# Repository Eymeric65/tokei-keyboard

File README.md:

# tokei-keyboard
Official repository of the Tokei split keyboard.

This repository is split in the different component in order to make a working Tokei Split keyboard.

*If you are searching the kicad library used in this keyboard you should go to [this repository]*

## Kicad / PCB 

If you directly want to order your board you should directly check [JLCPCB production archive](/kicad/OUTPUT/final-JLCPCB.zip)

Otherwise Kicad project is divided in three :
- The left half
- The right half
- The paneliser to reunion both for production

Electrical output is stored into the **`JLCPCB`** directory, CAD related output is stored in **`CAD`** folder (don't hesitate to check)

## firmware

The `firmware` folder contain ready to flash files in order to test right away the keyboard.

## ZMK

The `zmk-config` file is a direct copy of my `zmk-config` fork for this keyboard. It is the base to the build of the keyboard.

## CAD 

The `CAD` folder contain everything related with the 3D printed cover. I work with Alibre but you can find the ready-to-use `.step` in the `CAD/export` folder.

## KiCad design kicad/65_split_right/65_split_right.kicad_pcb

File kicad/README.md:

Here you can find both of the Kicad project for the right and left halves of the keyboard.
There is also the result of the paneliser in order to merge both halves (cheaper).

I would advise to check the board with your supplier.

If you trust me entirely you can directly use the archive [JLCPC accepted gerber](/OUTPUT/final-JLCPCB.zip) (for reference $32.37 for 5 boards)

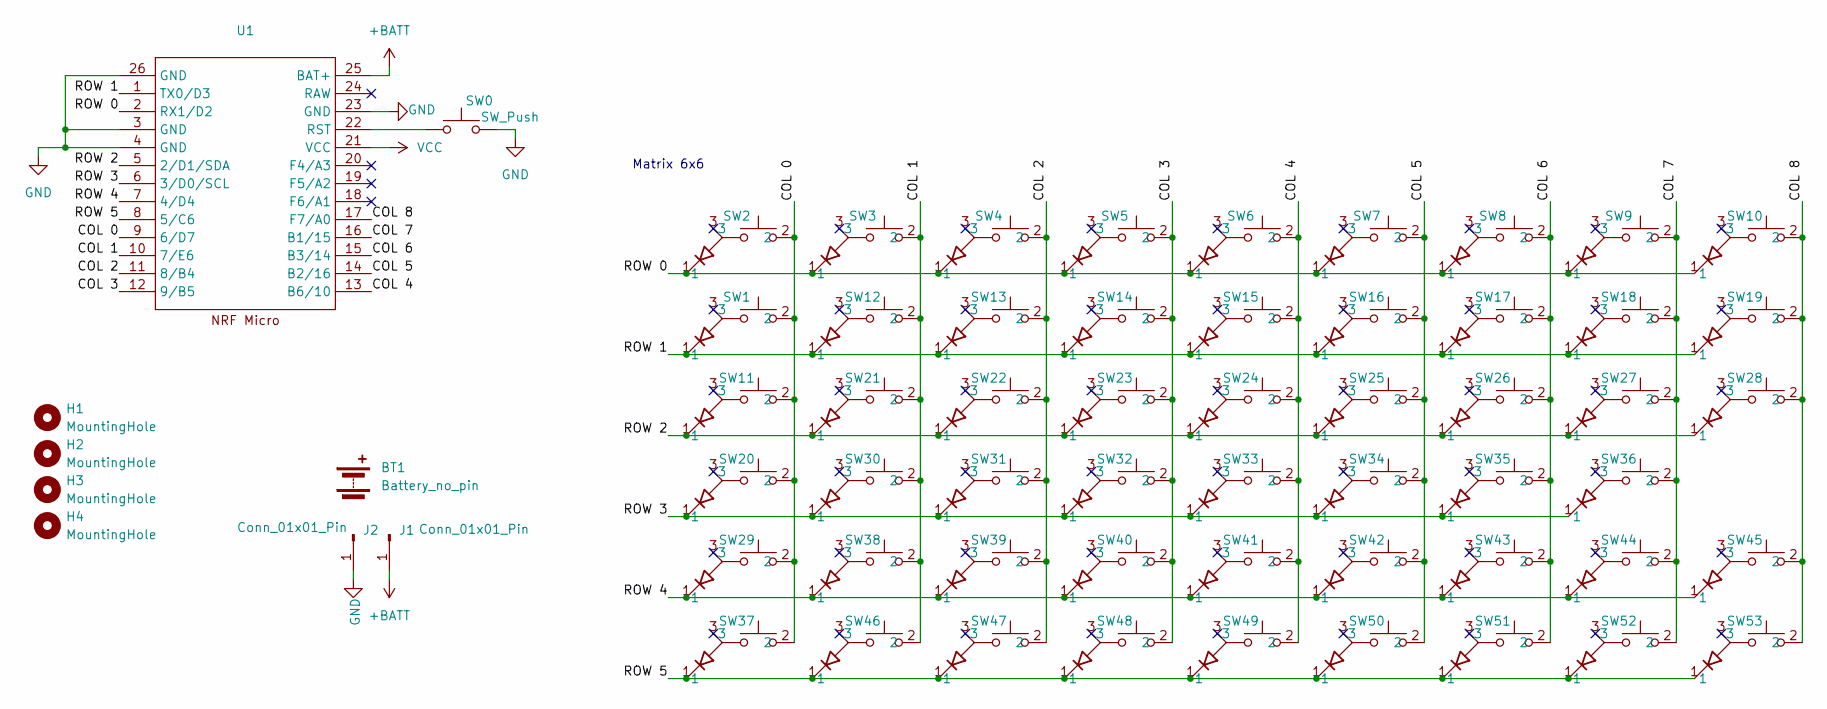
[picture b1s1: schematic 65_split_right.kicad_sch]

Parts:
BT1: Battery_no_pin; 503020 battery hole
H1, H2, H3, H4: MountingHole; MountingHole_2.2mm_M2_DIN965
J1, J2: Conn_01x01_Pin; Pin_D1.0mm_L10.0mm
SW0: SW_Push; Reset_Switch
SW1, SW2, SW3, SW4, SW5, SW6, SW7, SW8, SW9, SW10, SW11, SW12, SW13, SW14, SW15, SW16, SW17, SW19, SW20, SW21, SW22, SW23, SW24, SW25, SW26, SW28, SW29, SW30, SW31, SW32, SW33, SW34, SW36, SW37, SW38, SW39, SW40, SW41, SW42, SW44, SW45, SW47, SW48, SW49, SW50, SW51, SW52, SW53: SW_UNIVERSAL_1.00u_PCB
SW18, SW46: SW_UNIVERSAL_2.00u_PCB
SW27: SW_UNIVERSAL_1.50u_PCB
SW35: SW_UNIVERSAL_2.25u_PCB
SW43: SW_UNIVERSAL_1.75u_PCB
U1: ProMicro_DUAL

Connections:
+BATT: J1.1, U1.25 (BAT+)
/COL 0: SW1.2, SW2.2, SW11.2, SW20.2, SW29.2, SW37.2, U1.9 (6/D7)
/COL 1: SW3.2, SW12.2, SW21.2, SW30.2, SW38.2, SW46.2, U1.10 (7/E6)
/COL 2: SW4.2, SW13.2, SW22.2, SW31.2, SW39.2, SW47.2, U1.11 (8/B4)
/COL 3: SW5.2, SW14.2, SW23.2, SW32.2, SW40.2, SW48.2, U1.12 (9/B5)
/COL 4: SW6.2, SW15.2, SW24.2, SW33.2, SW41.2, SW49.2, U1.13 (B6/10)
/COL 5: SW7.2, SW16.2, SW25.2, SW34.2, SW42.2, SW50.2, U1.14 (B2/16)
/COL 6: SW8.2, SW17.2, SW26.2, SW35.2, SW43.2, SW51.2, U1.15 (B3/14)
/COL 7: SW9.2, SW18.2, SW27.2, SW36.2, SW44.2, SW52.2, U1.16 (B1/15)
/COL 8: SW10.2, SW19.2, SW28.2, SW45.2, SW53.2, U1.17 (F7/A0)
/ROW 0: SW2.1, SW3.1, SW4.1, SW5.1, SW6.1, SW7.1, SW8.1, SW9.1, SW10.1, U1.2 (RX1/D2)
/ROW 1: SW1.1, SW12.1, SW13.1, SW14.1, SW15.1, SW16.1, SW17.1, SW18.1, SW19.1, U1.1 (TX0/D3)
/ROW 2: SW11.1, SW21.1, SW22.1, SW23.1, SW24.1, SW25.1, SW26.1, SW27.1, SW28.1, U1.5 (2/D1/SDA)
/ROW 3: SW20.1, SW30.1, SW31.1, SW32.1, SW33.1, SW34.1, SW35.1, SW36.1, U1.6 (3/D0/SCL)
/ROW 4: SW29.1, SW38.1, SW39.1, SW40.1, SW41.1, SW42.1, SW43.1, SW44.1, SW45.1, U1.7 (4/D4)
/ROW 5: SW37.1, SW46.1, SW47.1, SW48.1, SW49.1, SW50.1, SW51.1, SW52.1, SW53.1, U1.8 (5/C6)
GND: J2.1, SW0.2, U1.3 (GND), U1.4 (GND), U1.23 (GND), U1.26 (GND)
unnamed: SW0.1, U1.22 (RST)
VCC: U1.21 (VCC)

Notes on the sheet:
Matrix 6x6

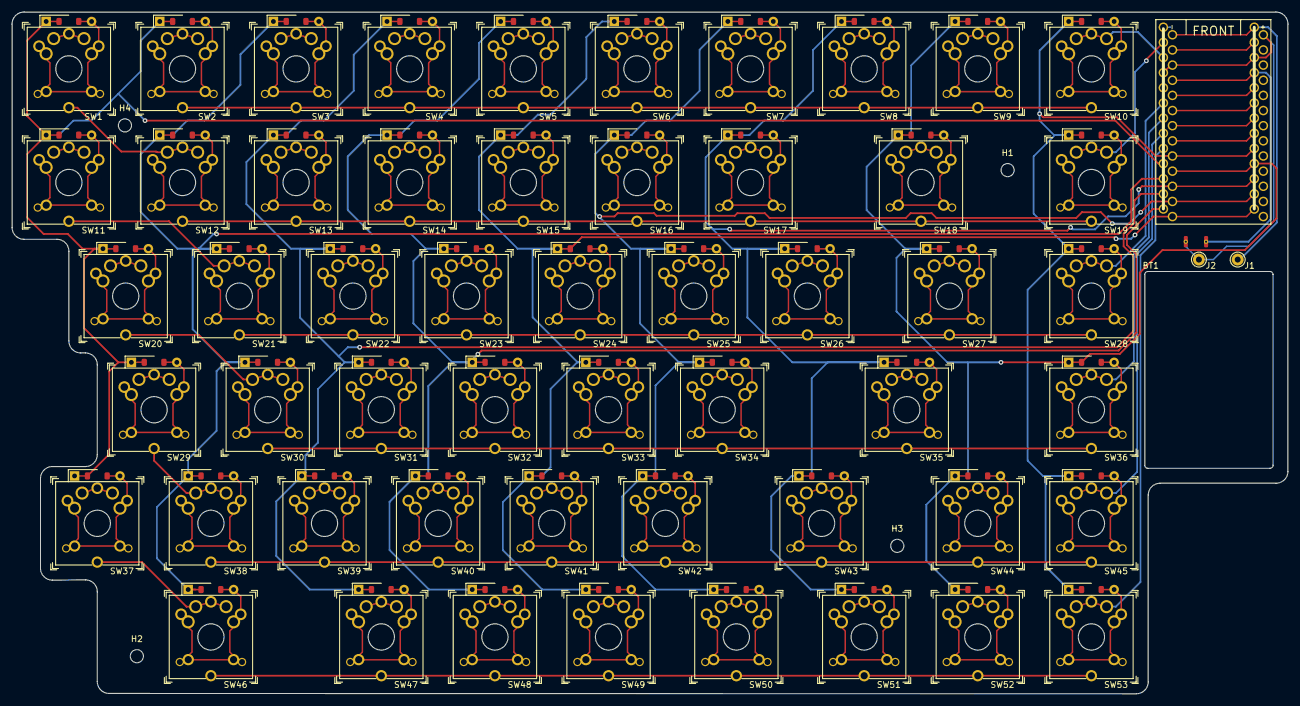
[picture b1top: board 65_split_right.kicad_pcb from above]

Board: 2 copper layers, 213.9 x 114.2 mm, 62 parts (1 on the bottom side), 18 nets.

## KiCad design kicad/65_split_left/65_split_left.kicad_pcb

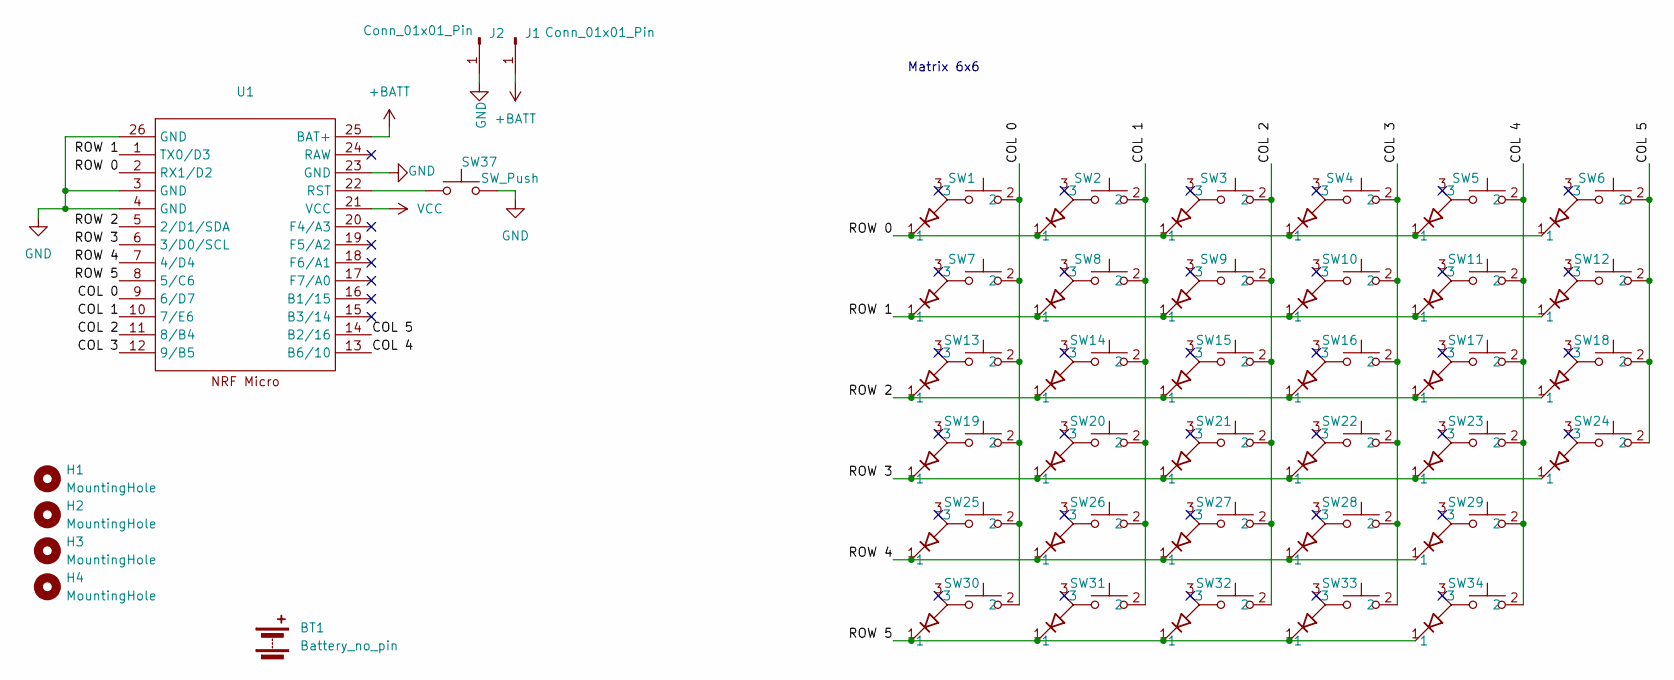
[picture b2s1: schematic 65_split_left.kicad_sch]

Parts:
BT1: Battery_no_pin; 503020 battery hole
H1, H2, H3, H4: MountingHole; MountingHole_2.2mm_M2_DIN965
J1, J2: Conn_01x01_Pin; Pin_D1.0mm_L10.0mm
SW1, SW2, SW3, SW4, SW5, SW6, SW7, SW8, SW9, SW10, SW11, SW12, SW14, SW15, SW16, SW17, SW18, SW20, SW21, SW22, SW23, SW24, SW26, SW27, SW28, SW29, SW30: SW_UNIVERSAL_1.00u_PCB
SW13: SW_UNIVERSAL_1.50u_PCB
SW19: SW_UNIVERSAL_1.75u_PCB
SW25: SW_UNIVERSAL_2.25u_PCB
SW31, SW32, SW33: SW_UNIVERSAL_1.25u_PCB
SW34: SW_UNIVERSAL_2.00u_PCB
SW37: SW_Push; Reset_Switch
U1: ProMicro_DUAL

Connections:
+BATT: J1.1, U1.25 (BAT+)
/COL 0: SW1.2, SW7.2, SW13.2, SW19.2, SW25.2, SW30.2, U1.9 (6/D7)
/COL 1: SW2.2, SW8.2, SW14.2, SW20.2, SW26.2, SW31.2, U1.10 (7/E6)
/COL 2: SW3.2, SW9.2, SW15.2, SW21.2, SW27.2, SW32.2, U1.11 (8/B4)
/COL 3: SW4.2, SW10.2, SW16.2, SW22.2, SW28.2, SW33.2, U1.12 (9/B5)
/COL 4: SW5.2, SW11.2, SW17.2, SW23.2, SW29.2, SW34.2, U1.13 (B6/10)
/COL 5: SW6.2, SW12.2, SW18.2, SW24.2, U1.14 (B2/16)
/ROW 0: SW1.1, SW2.1, SW3.1, SW4.1, SW5.1, SW6.1, U1.2 (RX1/D2)
/ROW 1: SW7.1, SW8.1, SW9.1, SW10.1, SW11.1, SW12.1, U1.1 (TX0/D3)
/ROW 2: SW13.1, SW14.1, SW15.1, SW16.1, SW17.1, SW18.1, U1.5 (2/D1/SDA)
/ROW 3: SW19.1, SW20.1, SW21.1, SW22.1, SW23.1, SW24.1, U1.6 (3/D0/SCL)
/ROW 4: SW25.1, SW26.1, SW27.1, SW28.1, SW29.1, U1.7 (4/D4)
/ROW 5: SW30.1, SW31.1, SW32.1, SW33.1, SW34.1, U1.8 (5/C6)
GND: J2.1, SW37.2, U1.3 (GND), U1.4 (GND), U1.23 (GND), U1.26 (GND)
unnamed: SW37.1, U1.22 (RST)
VCC: U1.21 (VCC)

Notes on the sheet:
Matrix 6x6

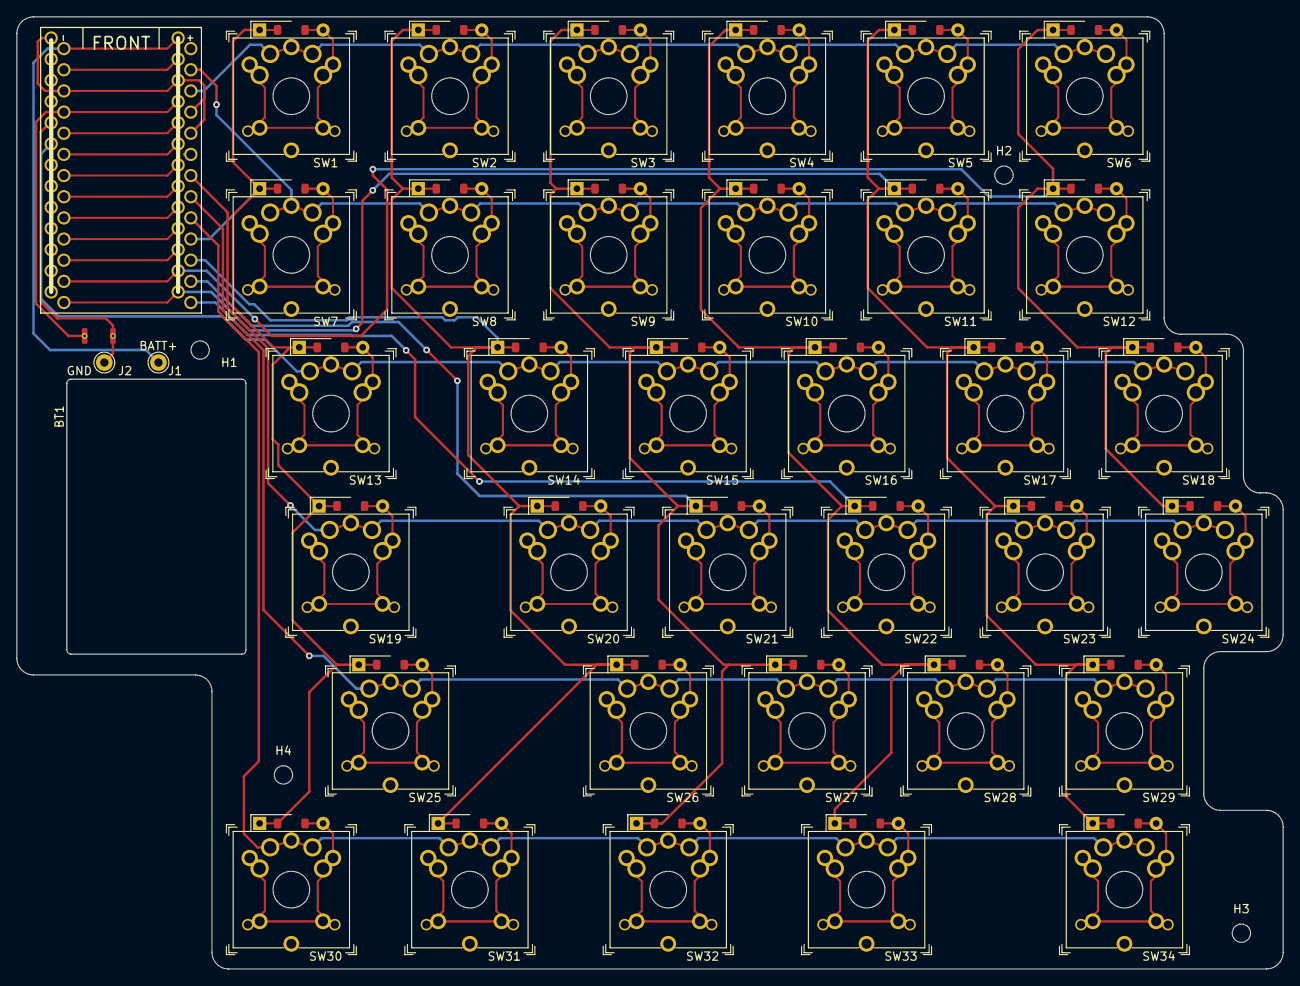
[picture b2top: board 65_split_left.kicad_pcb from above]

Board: 2 copper layers, 151.9 x 114.2 mm, 43 parts (1 on the bottom side), 15 nets.

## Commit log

2025-05-24 Add everything
